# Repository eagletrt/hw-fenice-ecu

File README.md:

# ECU - hardware

ECU hardware design of the E-Agle Trento Racing Team car which run on Fenice.

## Contributors

- Filippo Volpe

## Documentation

Documentation can be found under [`./docs/DAS_ECU.md`](./docs/DAS_ECU.md)

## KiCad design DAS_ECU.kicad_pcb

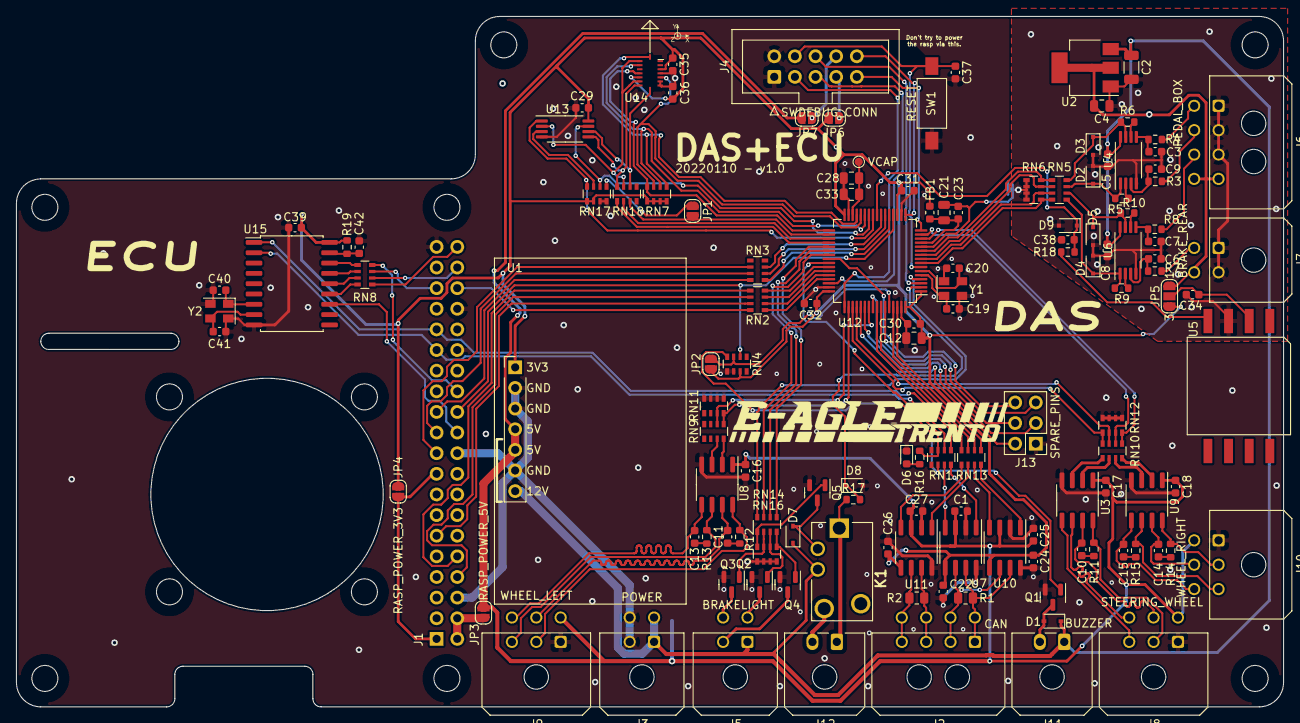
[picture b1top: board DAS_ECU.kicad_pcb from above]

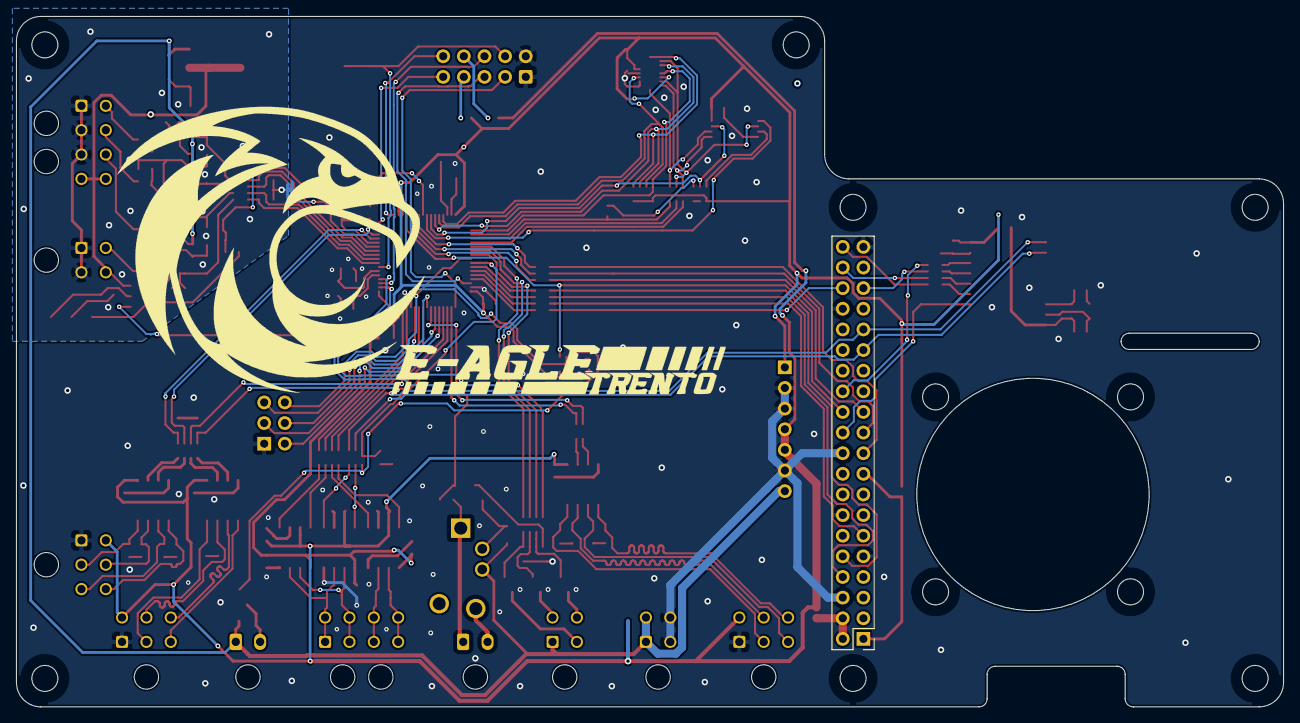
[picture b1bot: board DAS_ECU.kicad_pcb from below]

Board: 2 copper layers, 156.0 x 85.0 mm, 145 parts (2 on the bottom side), 154 nets.

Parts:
C1, C3, C5, C6, C7, C8, C9, C16, C17, C18, C22, C23, C24, C25, C26, C27, C29, C30, C31, C32, C34, C35, C36, C37, C38, C39, C42: 100nF; C_0603_1608Metric
C2: 10uF; C_1206_3216Metric
C4, C21, C28, C33: 1uF; C_0805_2012Metric
C10, C11, C13, C14, C15: 10nF; C_0603_1608Metric
C12: 4.7uF; C_0805_2012Metric
C19, C20, C40, C41: 20pF; C_0603_1608Metric
D1, D7: 1N4148W; D_SOD-323
D2, D3, D4, D5: DDZ5V1ASF 5V1; D_SOD-323F
D6: LED; LED_0603_1608Metric
D8, D9: DDZ3V3ASF 3V3; D_SOD-323F
FB1: 220R @ 100MHz; L_0603_1608Metric
H1, H2, H3, H4, H5, H6, H7, H8, H9, H10, H11: MountingHole; MountingHole_3.2mm_M3_ISO14580
J1: Raspberry_Pi_2_3; raspberrypi_hat_template
J2: CAN; Molex_Micro-Fit_3.0_43045-0800_2x04_P3.00mm_Horizontal
J3: POWER; Molex_Micro-Fit_3.0_43045-0400_2x02_P3.00mm_Horizontal
J4: SWDEBUG_CONN; IDC-Header_2x05_P2.54mm_Vertical
J5: BRAKELIGHT; Molex_Micro-Fit_3.0_43045-0400_2x02_P3.00mm_Horizontal
J6: PEDAL_BOX; Molex_Micro-Fit_3.0_43045-0800_2x04_P3.00mm_Horizontal
J7: BRAKE_REAR; Molex_Micro-Fit_3.0_43045-0400_2x02_P3.00mm_Horizontal
J8: STEERING_WHEEL; Molex_Micro-Fit_3.0_43045-0600_2x03_P3.00mm_Horizontal
J9: WHEEL_LEFT; Molex_Micro-Fit_3.0_43045-0600_2x03_P3.00mm_Horizontal
J10: WHEEL_RIGHT; Molex_Micro-Fit_3.0_43045-0600_2x03_P3.00mm_Horizontal
J11: BUZZER; Molex_Micro-Fit_3.0_43650-0200_1x02_P3.00mm_Horizontal
J12: SD; Molex_Micro-Fit_3.0_43650-0200_1x02_P3.00mm_Horizontal
J13: SPARE_PINS; PinHeader_2x03_P2.54mm_Vertical
JP1, JP2, JP6, JP7: SolderJumper_2_Open; SolderJumper-2_P1.3mm_Open_RoundedPad1.0x1.5mm
JP3: RASP_POWER_5V; SolderJumper-2_P1.3mm_Open_RoundedPad1.0x1.5mm
JP4: RASP_POWER_3V3; SolderJumper-2_P1.3mm_Open_RoundedPad1.0x1.5mm
JP5: SolderJumper_3; SolderJumper-3_P1.3mm_Open_RoundedPad1.0x1.5mm_NumberLabels
K1: EX12U1S
NT1: Net-Tie_2; connecting_trace_0.6mm
Q1, Q2, Q3, Q4, Q5: 2N7002NXAKR; SOT-23
R1, R2: 120; R_0805_2012Metric
R3, R4, R7, R8, R18: 100; R_0603_1608Metric
R5, R6, R9, R10: 1k8; R_0603_1608Metric
R11, R12, R13, R14, R15: 120R; R_0603_1608Metric
R16: 1k; R_0603_1608Metric
R17: 1M; R_0603_1608Metric
R19: 100k; R_0603_1608Metric
RN1, RN2, RN3, RN8, RN13, RN14, RN18: 33; R_Array_Convex_4x0603
RN4, RN7, RN16, RN17: 100k; R_Array_Convex_4x0603
RN5, RN9, RN10: 10k; R_Array_Convex_4x0603
RN6, RN11, RN12: 18k; R_Array_Convex_4x0603
SW1: RESET; SW_SPST_FSMSM
TP1: VCAP; TestPoint_Pad_D1.0mm
U1: Tex_DCDC_v2; Tex_DCDC_v2_horizontal
U2: LD1117S50TR_SOT223; SOT-223-3_TabPin2
U3: MAX490E; SOIC-8_3.9x4.9mm_P1.27mm
U4, U6: LM358PWR; TSSOP-8_4.4x3mm_P0.65mm
U5: MP3V5004DP; NXP_CASE_1351-01
U7, U10, U11: MCP2562-E-SN; SOIC-8_3.9x4.9mm_P1.27mm
U8, U9: UA9637A; SOIC-8_3.9x4.9mm_P1.27mm
U12: STM32F446RETx; LQFP-64_10x10mm_P0.5mm
U13: M95256-WMN6P; TSSOP-8_4.4x3mm_P0.65mm
U14: BMI088; Bosch_LGA-16_3x4.5mm_P0.5mm
U15: MCP2515-xSO; SOIC-18W_7.5x11.6mm_P1.27mm
Y1, Y2: ECS-160-18-33 16Mhz; Crystal_SMD_EuroQuartz_MT-4Pin_3.2x2.5mm

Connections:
+3V3: C12.1, C22.1, C24.1, C26.1, C29.1, C30.1, C31.1, C32.1, C35.1, C36.1, C39.1, FB1.1, JP2.1, JP4.2, JP5.3, JP6.2, R19.1, RN4.7, RN7.5, RN7.6, RN7.7, RN7.8, RN17.5, RN17.6, U1.1, U7.5, U10.5, U11.5, U12.1, U12.19, U12.32, U12.48, U12.64, U13.8, U14.3, U14.11, U15.18
+5V: C1.1, C16.1, C17.1, C18.1, C25.1, C27.1, J8.4, J9.4, J10.4, JP3.2, JP7.2, U1.4, U1.5, U3.1, U7.3, U8.1, U9.1, U10.3, U11.3
+12V: C2.1, C5.2, C8.2, D1.1, D7.1, J3.1, J3.3, J5.1, J11.1, K1.3, U1.7, U2.3, U4.8, U6.8
/Analog_Sensors/5V_SENSORS: C4.1, J6.4, J6.8, J7.4, JP5.1, U2.2
/Analog_Sensors/ACC_1_BUF: D3.1, R6.1, RN5.8, U4.7
/Analog_Sensors/ACC_2_BUF: D2.1, R5.1, RN5.7, U4.1
/Analog_Sensors/ACC_S1: J6.5, R4.2
/Analog_Sensors/ACC_S2: J6.6, R3.2
/Analog_Sensors/BRAKE_F: RN5.3, RN6.6, U12.9
/Analog_Sensors/BRAKE_F_BUF: D5.1, R10.1, RN5.6, U6.7
/Analog_Sensors/BRAKE_R_BUF: D4.1, R9.1, RN5.5, U6.1
/Analog_Sensors/BRAKE_SF: J6.7, R8.2
/Analog_Sensors/BRAKE_SR: J7.3, R7.2
/Analog_Sensors/PITOT_PD: C38.1, D9.1, R18.1, U12.24
/BL_CH1: RN14.1, U12.37
/BL_CH1_G: Q4.1, RN14.8, RN16.1
/BL_CH2: RN14.2, U12.38
/BL_CH2_G: Q2.1, RN14.7, RN16.2
/BL_CH3: RN14.3, U12.39
/BL_CH3_G: Q3.1, RN14.6, RN16.3
/BRAKELIGHT_CH1: J5.2, Q4.3
/BRAKELIGHT_CH2: J5.3, Q2.3
/BRAKELIGHT_CH3: J5.4, Q3.3
/Brain_Rasp/3V3_FT: C21.1, C23.1, FB1.2, U12.13
/Brain_Rasp/ACCS_CH1: RN5.1, RN6.8, U12.11
/Brain_Rasp/ACCS_CH2: RN5.2, RN6.7, U12.10
/Brain_Rasp/ACC_INT: RN7.1, U12.29, U14.16
/Brain_Rasp/BOOT0: JP2.2, RN4.3, U12.60
/Brain_Rasp/BRAKE_PRESSURE_FRONT: RN5.4, RN6.5, U12.8
/Brain_Rasp/BUZZER: R16.1, RN1.3, U12.41
/Brain_Rasp/BUZZER_1: Q1.1, RN1.6, RN4.4
/Brain_Rasp/CAN1_RX: RN13.6, U12.61
/Brain_Rasp/CAN1_TX: RN13.5, U12.62
/Brain_Rasp/CAN2_RX: RN13.8, U12.57
/Brain_Rasp/CAN2_TX: RN13.7, U12.58
/Brain_Rasp/CANRX_NVIDIA: J1.29, RN1.2, U15.2
/Brain_Rasp/CANTX_NVIDIA: J1.31, RN1.1, U15.1
/Brain_Rasp/CSB_ACC: RN7.2, U12.27, U14.14
/Brain_Rasp/CSB_GYR: RN7.3, U12.28, U14.5
/Brain_Rasp/GYR_INT: RN7.4, U12.33, U14.12
/Brain_Rasp/MCU_CTS: RN2.2, U12.44
/Brain_Rasp/MCU_RTS: RN2.1, U12.45
/Brain_Rasp/MCU_RX: RN2.3, U12.43
/Brain_Rasp/MCU_SPI_CLK: RN3.5, U12.21
/Brain_Rasp/MCU_SPI_CS: J1.24, RN4.2, U12.20
/Brain_Rasp/MCU_SPI_MISO: RN3.6, U12.22
/Brain_Rasp/MCU_SPI_MOSI: RN3.7, U12.23
/Brain_Rasp/MCU_TX: RN2.4, U12.42
/Brain_Rasp/PB4: J13.4, U12.56
/Brain_Rasp/PB7: J13.5, U12.59
/Brain_Rasp/PC9: J13.6, U12.40
/Brain_Rasp/PC12: J13.2, U12.53
/Brain_Rasp/PD2: J13.3, U12.54
/Brain_Rasp/RASP_CAN_CS: J1.26, RN8.4
/Brain_Rasp/RASP_CAN_CS_1: RN8.5, U15.16
/Brain_Rasp/RASP_CTS: J1.36, RN2.8
/Brain_Rasp/RASP_RTS: J1.11, RN2.7
/Brain_Rasp/RASP_RX: J1.10, RN2.5
/Brain_Rasp/RASP_SPI1_CLK: J1.40, RN8.1
/Brain_Rasp/RASP_SPI1_CLK_1: RN8.8, U15.13
/Brain_Rasp/RASP_SPI1_MISO: J1.35, RN8.3
/Brain_Rasp/RASP_SPI1_MISO_1: RN8.6, U15.15
/Brain_Rasp/RASP_SPI1_MOSI: J1.38, RN8.2
/Brain_Rasp/RASP_SPI1_MOSI_1: RN8.7, U15.14
/Brain_Rasp/RASP_SPI_CLK: J1.23, RN3.4
/Brain_Rasp/RASP_SPI_MISO: J1.21, RN3.3
/Brain_Rasp/RASP_SPI_MOSI: J1.19, RN3.2
/Brain_Rasp/RASP_TX: J1.8, RN2.6
/Brain_Rasp/SPI2_MISO: RN18.2, U12.35
/Brain_Rasp/SPI2_MOSI: RN18.1, U12.36
/Brain_Rasp/SPI2_SCK: JP1.1, RN18.3, U12.34
/Brain_Rasp/SW_CLK: RN10.4, RN12.5, U12.51
/Brain_Rasp/SW_DATA: RN10.3, RN12.6, U12.52
/Brain_Rasp/VCAP_1: C28.2, C33.2, TP1.1, U12.30
/Brain_Rasp/WL_A: RN9.1, RN11.8, U12.50
/Brain_Rasp/WL_B: RN9.2, RN11.7, U12.55
/Brain_Rasp/WR_A: RN10.1, RN12.8, U12.14
/Brain_Rasp/WR_B: RN10.2, RN12.7, U12.15
/Brain_Rasp/~CS_EEPROM: RN17.4, U12.25, U13.1
/Brain_Rasp/~HOLD: RN17.2, U12.26, U13.7
/Brain_Rasp/~INT: J1.22, U15.12
/Brain_Rasp/~W: RN17.3, U13.3
/CAN1_N: J2.2, J2.6, R1.2, U7.6, U10.6
/CAN1_P: J2.1, J2.5, R1.1, U7.7, U10.7
/CAN2_N: J2.4, J2.8, R2.2, U11.6
/CAN2_P: J2.3, J2.7, R2.1, U11.7
/Encoders/SW_CLK+: J8.3, U3.5
/Encoders/SW_CLK-: J8.6, U3.6
/Encoders/SW_CLK_5: RN10.5, U3.3
/Encoders/SW_DATA+: J8.2, R11.2, U3.8
/Encoders/SW_DATA-: C10.1, J8.5, U3.7
/Encoders/SW_DATA_5: RN10.6, U3.2
/Encoders/WL_A+: J9.2, R12.2, U8.8
/Encoders/WL_A-: C11.1, J9.5, U8.7
/Encoders/WL_A_5: RN9.8, U8.2
/Encoders/WL_B+: J9.3, R13.2, U8.6
/Encoders/WL_B-: C13.1, J9.6, U8.5
/Encoders/WL_B_5: RN9.7, U8.3
/Encoders/WR_A+: J10.2, R14.2, U9.8
/Encoders/WR_A-: C14.1, J10.5, U9.7
/Encoders/WR_A_5: RN10.8, U9.2
/Encoders/WR_B+: J10.3, R15.2, U9.6
/Encoders/WR_B-: C15.1, J10.6, U9.5
/Encoders/WR_B_5: RN10.7, U9.3
/IMU/MISO: RN18.7, U13.2, U14.10, U14.15
/IMU/MOSI: RN18.8, U13.5, U14.9
/IMU/SCK: RN18.6, U13.6, U14.8
/MCU_GPIO: J4.6, U12.3
/MCU_RX: J4.10, U12.17
/MCU_TX: J4.9, U12.16
/SD_CLOSE: RN14.4, U12.4
/SD_CLOSE_G: Q5.1, RN14.5, RN16.4
/SD_IN: J12.1, K1.1, R17.1
/SD_IN_3V3: D8.1, R17.2, U12.2
/SD_OUT: J12.2, K1.4
/SWCLK: J4.3, U12.49
/SWDIO: J4.5, U12.46
/~RST: C37.1, J4.4, SW1.1, U12.7
GND: C1.2, C12.2, C16.2, C17.2, C18.2, C19.2, C20.2, C22.2, C24.2, C25.2, C26.2, C27.2, C28.1, C29.2, C30.2, C31.2, C32.2, C33.1, C35.2, C36.2, C37.2, C39.2, C40.2, C41.2, C42.1, D6.1, D8.2, J1.6, J1.9, J1.14, J1.20, J1.25, J1.30, J1.34, J1.39, J3.2, J3.4, J4.1, J4.2, J8.1, J9.1, J10.1, J13.1, NT1.2, Q1.2, Q2.2, Q3.2, Q4.2, Q5.2, RN4.5, RN4.6, RN11.1, RN11.2, RN11.3, RN11.4, RN12.1, RN12.2, RN12.3, RN12.4, RN16.5, RN16.6, RN16.7, RN16.8, RN17.7, RN17.8, SW1.2, U1.2, U1.3, U1.6, U3.4, U7.2, U7.8, U8.4, U9.4, U10.2, U10.8, U11.2, U11.8, U12.18, U12.31, U12.47, U12.63, U13.4, U14.4, U14.6, U14.7, U15.9, Y1.2, Y1.4, Y2.2, Y2.4
GND1: C2.2, C3.2, C4.2, C5.1, C6.2, C7.2, C8.1, C9.2, C21.2, C23.2, C34.2, C38.2, D2.2, D3.2, D4.2, D5.2, D9.2, J6.1, J6.2, J6.3, J7.1, J7.2, NT1.1, RN6.1, RN6.2, RN6.3, RN6.4, U2.1, U4.4, U5.3, U6.4, U12.12
unnamed: C3.1, R4.1, U4.5
unnamed: C6.1, R7.1, U6.3
unnamed: C7.1, R8.1, U6.5
unnamed: C9.1, R3.1, U4.3
unnamed: C10.2, R11.1
unnamed: C11.2, R12.1
unnamed: C13.2, R13.1
unnamed: C14.2, R14.1
unnamed: C15.2, R15.1
unnamed: C19.1, U12.5, Y1.1
unnamed: C20.1, U12.6, Y1.3
unnamed: C34.1, JP5.2, U5.2
unnamed: C40.1, U15.7, Y2.1
unnamed: C41.1, U15.8, Y2.3
unnamed: C42.2, R19.2, U15.17
unnamed: D1.2, J11.2, Q1.3
unnamed: D6.2, R16.2
unnamed: D7.2, K1.2, Q5.3
unnamed: J1.1, J1.17, JP4.1
unnamed: J1.2, J1.4, JP3.1
unnamed: J4.7, JP6.1
unnamed: J4.8, JP7.1
unnamed: JP1.2, RN17.1
unnamed: R5.2, U4.2
unnamed: R6.2, U4.6
unnamed: R9.2, U6.2
unnamed: R10.2, U6.6
unnamed: R18.2, U5.4
unnamed: RN1.7, U7.4
unnamed: RN1.8, U7.1
unnamed: RN13.1, U11.4
unnamed: RN13.2, U11.1
unnamed: RN13.3, U10.4
unnamed: RN13.4, U10.1

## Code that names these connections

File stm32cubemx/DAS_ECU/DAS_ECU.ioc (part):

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Mcu.Name=STM32F446R(C-E)Tx
Mcu.Package=LQFP64
Mcu.UserName=STM32F446RETx
PA0-WKUP.Signal=S_TIM5_CH1
PA1.Signal=S_TIM5_CH2
PA10.Mode=Asynchronous
PA10.Signal=USART1_RX
PA11.Mode=CTS_RTS
PA11.Signal=USART1_CTS
PA12.Mode=CTS_RTS
PA12.Signal=USART1_RTS
PA13.Mode=Serial_Wire
PA13.Signal=SYS_JTMS-SWDIO
PA14.Mode=Serial_Wire
PA14.Signal=SYS_JTCK-SWCLK
PA15.Signal=S_TIM2_CH1_ETR
PA2.Mode=Asynchronous
PA2.Signal=USART2_TX
PA3.Mode=Asynchronous
PA3.Signal=USART2_RX
PA4.Mode=NSS_Signal_Hard_Input
PA4.Signal=SPI1_NSS
PA5.Mode=Full_Duplex_Slave
PA5.Signal=SPI1_SCK
PA6.Mode=Full_Duplex_Slave
PA6.Signal=SPI1_MISO
PA7.Mode=Full_Duplex_Slave
PA7.Signal=SPI1_MOSI
PA8.Signal=S_TIM1_CH1
PA9.Mode=Asynchronous
PA9.Signal=USART1_TX
PB0.Signal=GPIO_Output
PB1.Signal=GPIO_Output
PB10.Signal=GPXTI10
PB12.Signal=GPXTI12
PB13.Mode=Full_Duplex_Master
PB13.Signal=SPI2_SCK
PB14.Mode=Full_Duplex_Master
PB14.Signal=SPI2_MISO
PB15.Mode=Full_Duplex_Master
PB15.Signal=SPI2_MOSI
PB2.Signal=GPIO_Output
PB3.Signal=S_TIM2_CH2
PB5.Mode=CAN_Activate
PB5.Signal=CAN2_RX
PB6.Mode=CAN_Activate
PB6.Signal=CAN2_TX
PB8.Mode=CAN_Activate
PB8.Signal=CAN1_RX
PB9.Mode=CAN_Activate
PB9.Signal=CAN1_TX
PC0.Signal=ADCx_IN10
PC1.Signal=ADCx_IN11
PC10.Mode=RX_Only_Simplex_Unidirect_Master
PC10.Signal=SPI3_SCK
PC11.Mode=RX_Only_Simplex_Unidirect_Master
PC11.Signal=SPI3_MISO
PC13.Signal=GPIO_Input
PC14-OSC32_IN.Signal=GPIO_Output
PC15-OSC32_OUT.Signal=GPIO_Output
PC2.Signal=ADCx_IN12
PC3.Signal=ADCx_IN13
PC4.Signal=ADCx_IN14
PC5.Signal=GPIO_Output
PC6.Signal=S_TIM3_CH1
PC7.Signal=S_TIM3_CH2
PC8.Signal=S_TIM3_CH3
PH0-OSC_IN.Mode=HSE-External-Oscillator
PH0-OSC_IN.Signal=RCC_OSC_IN
PH1-OSC_OUT.Mode=HSE-External-Oscillator
PH1-OSC_OUT.Signal=RCC_OSC_OUT
board=custom

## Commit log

2021-12-13 added readme and gitignore
2021-12-13 in progress push, still laying down preliminary schematic
2021-12-15 some other progress 2021-12-15
2021-12-24 added MCU requirements and solution section
2021-12-25 moved configuration to the F446 mcu, added docs on that
2022-01-05 modification of the schematic
2022-01-05 added all footprints, starting board
2022-01-05 corrected wrong connections
2022-01-05 started board, some corrections on schematic
2022-01-06 more progrees on board
2022-01-07 added board outline drawing
2022-01-07 added datasheet
2022-01-08 added IMU, pressure sensor, progress on board
2022-01-10 Board finished electrically, passes ERC/DRC
2022-01-10 Print ready v1.0
2022-01-14 changed to LM358PWR
2022-01-23 added MCP2515
2022-02-10 docs: format for wiki
2022-02-21 updated pdb schematic
2022-03-12 add note for how to connect encoder to board
2022-03-17 removed kicad v5 files
2022-03-17 converted to kicad v6
2022-03-17 Updated gitignore
2022-08-25 fix wrong data on encoder
2022-11-28 Documentation: - added info in readme - added license - added documentation and images
2023-06-20 updated license
